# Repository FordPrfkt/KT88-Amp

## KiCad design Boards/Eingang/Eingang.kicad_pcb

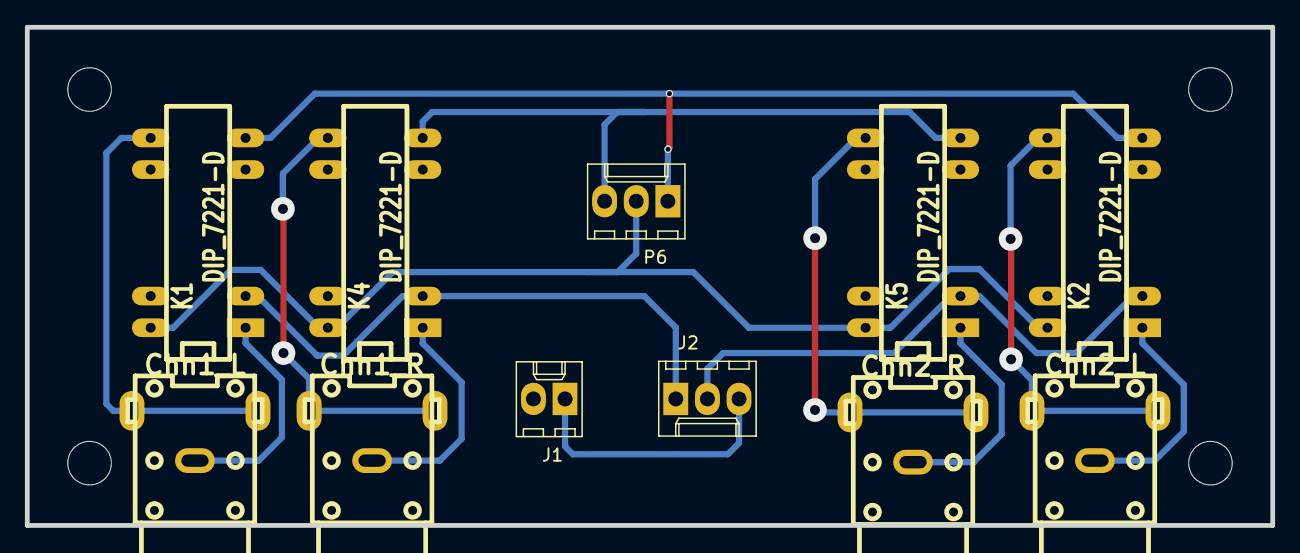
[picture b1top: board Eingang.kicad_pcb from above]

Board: 2 copper layers, 100.0 x 40.0 mm, 11 parts (0 on the bottom side), 15 nets.

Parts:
J1: 12V_Sup; Molex_KK-6410-02_02x2.54mm_Straight
J2: Chn_Switch; Molex_KK-6410-03_03x2.54mm_Straight
K1, K2, K4, K5: DIP_7221-D; REED
P6: LF_Out; Molex_KK-6410-03_03x2.54mm_Straight
P10: Chn1_L; rca_red
P11: Chn1_R; rca_white
P12: Chn2_L; rca_red
P13: Chn2_R; rca_white

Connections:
GND: J1.2, K1.6, K2.6, K4.6, K5.6
unnamed: J1.1, J2.3
unnamed: J2.1, K1.2, K4.2
unnamed: J2.2, K2.2, K5.2
unnamed: K1.1, P10.1
unnamed: K1.7, K2.7, P6.1
unnamed: K1.8, P10.2
unnamed: K1.14, K2.14, K4.14, K5.14, P6.2
unnamed: K2.1, P12.1
unnamed: K2.8, P12.2
unnamed: K4.1, P11.1
unnamed: K4.7, K5.7, P6.3
unnamed: K4.8, P11.2
unnamed: K5.1, P13.1
unnamed: K5.8, P13.2

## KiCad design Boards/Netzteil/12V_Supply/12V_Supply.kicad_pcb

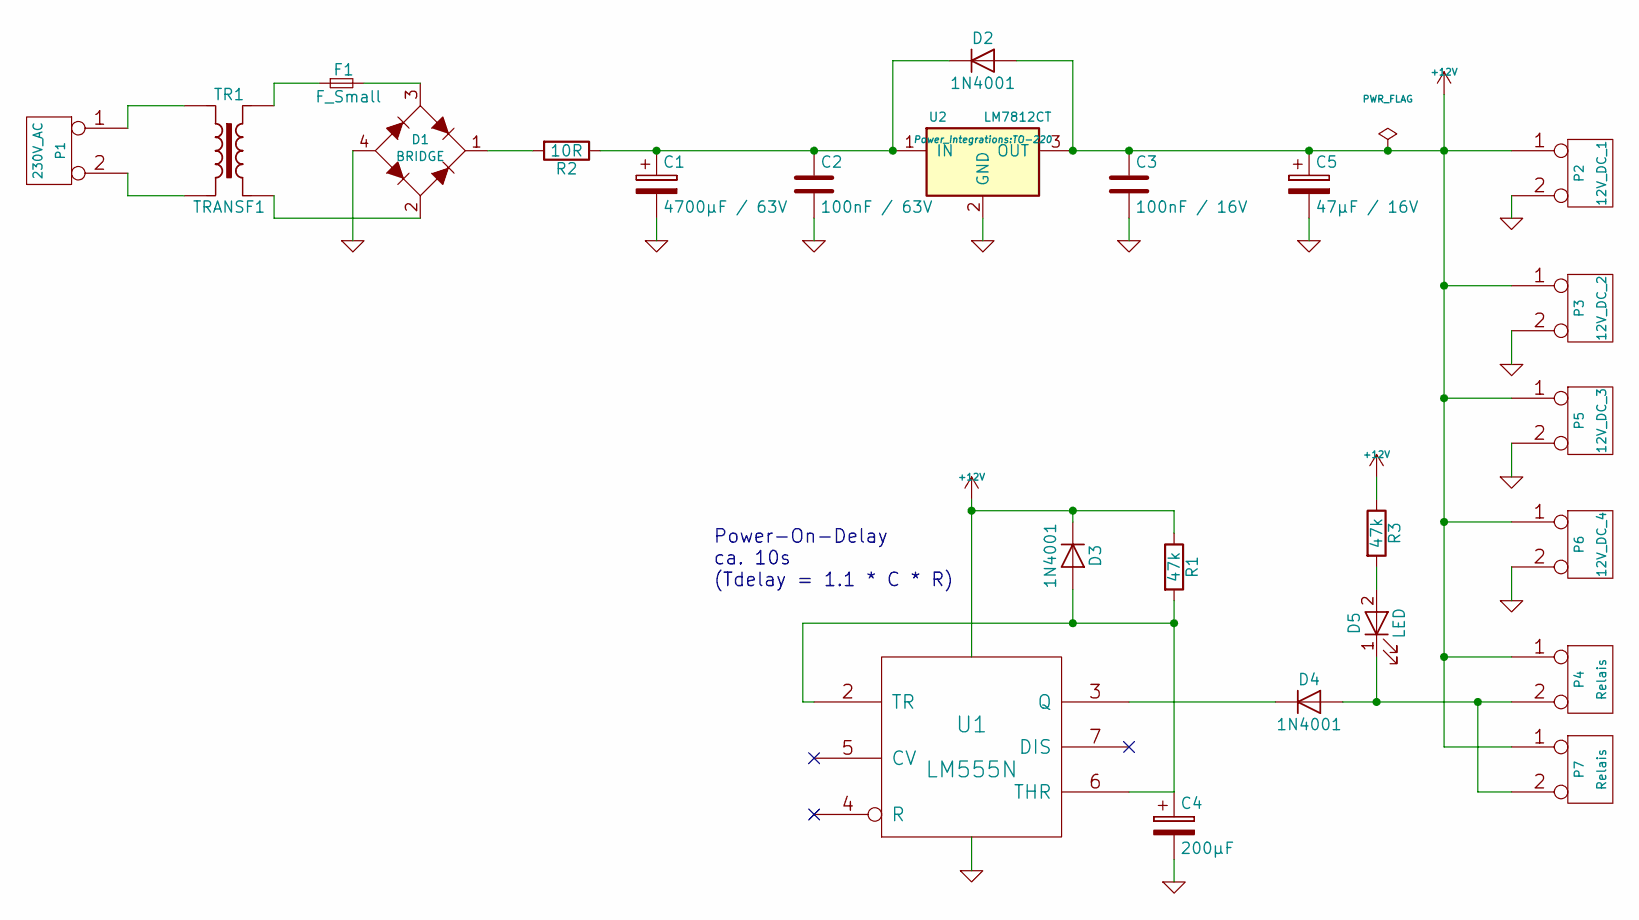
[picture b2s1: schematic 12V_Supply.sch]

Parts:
C1: 4700µF / 63V; CP_16x20mm
C2: 100nF / 63V; C_Disc_D3.0mm_W2.0mm_P2.50mm
C3: 100nF / 16V; C_Disc_D3.0mm_W2.0mm_P2.50mm
C4: 200µF; CP_4x5mm
C5: 47µF / 16V; CP_8x15mm
D1: BRIDGE; bridge_DFM
D2, D3, D4: 1N4001; diode_do41
D5: LED; LED_D3.0mm
F1: F_Small; fuse_holder_CQ-2
P1: 230V_AC; gmkds_3-2-7,62
P2: 12V_DC_1; MiniUniversalMate-N-LokSocket_2PinVertical
P3: 12V_DC_2; MiniUniversalMate-N-LokSocket_2PinVertical
P4, P7: Relais; kk156_26-60-4020
P5: 12V_DC_3; MiniUniversalMate-N-LokSocket_2PinVertical
P6: 12V_DC_4; MiniUniversalMate-N-LokSocket_2PinVertical
R1, R3: 47k; R_Axial_DIN0207_L6.3mm_D2.5mm_P10.16mm_Horizontal
R2: 10R; R_Axial_DIN0207_L6.3mm_D2.5mm_P10.16mm_Horizontal
TR1: TRANSF1; Transfo-simple
U1: LM555N; dil_8-300
U2: LM7812CT; TO-220

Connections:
+12V: C3.1, C5.1, D2.2 (A), D3.1 (K), P2.1, P3.1, P4.1, P5.1, P6.1, P7.1, R1.1, R3.1, U1.8 (VCC), U2.3 (OUT)
GND: C1.2, C2.2, C3.2, C4.2, C5.2, D1.4 (V-), P2.2, P3.2, P5.2, P6.2, U1.1 (GND), U2.2 (GND)
unnamed: C1.1, C2.1, D2.1 (K), R2.1, U2.1 (IN)
unnamed: C4.1, D3.2 (A), R1.2, U1.2 (TR), U1.6 (THR)
unnamed: D1.1 (V+), R2.2
unnamed: D1.2 (~1), TR1.3
unnamed: D1.3 (~2), F1.2
unnamed: D4.1 (K), U1.3 (Q)
unnamed: D4.2 (A), D5.1 (K), P4.2, P7.2
unnamed: D5.2 (A), R3.2
unnamed: F1.1, TR1.4
unnamed: P1.1, TR1.1
unnamed: P1.2, TR1.2

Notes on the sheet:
Power-On-Delay ca. 10s (Tdelay = 1.1 * C * R)

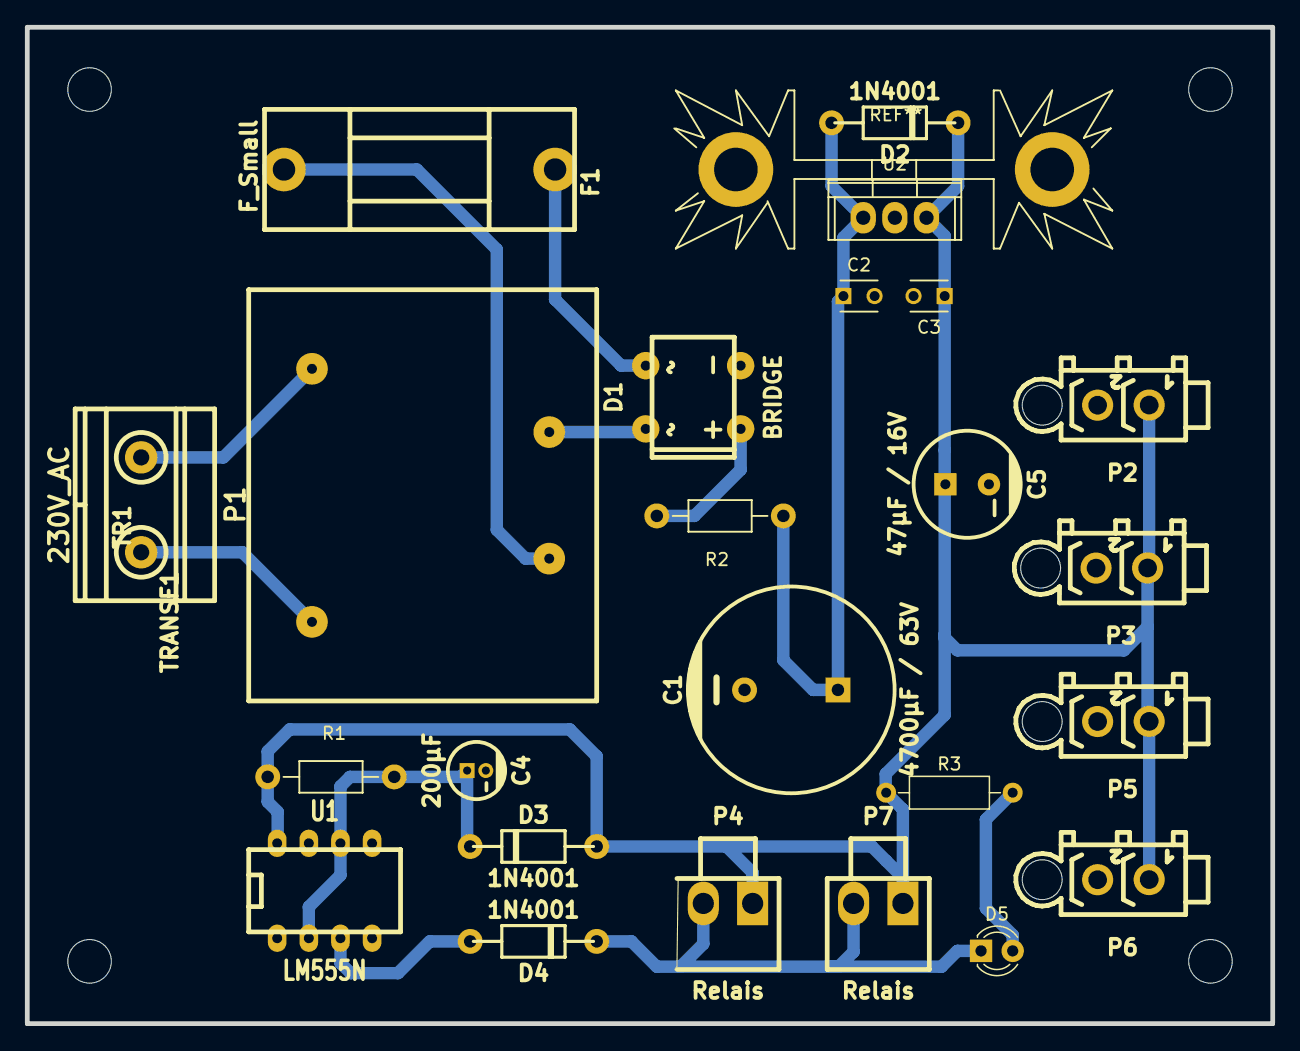
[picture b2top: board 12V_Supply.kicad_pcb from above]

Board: 2 copper layers, 100.0 x 80.0 mm, 24 parts (0 on the bottom side), 13 nets.

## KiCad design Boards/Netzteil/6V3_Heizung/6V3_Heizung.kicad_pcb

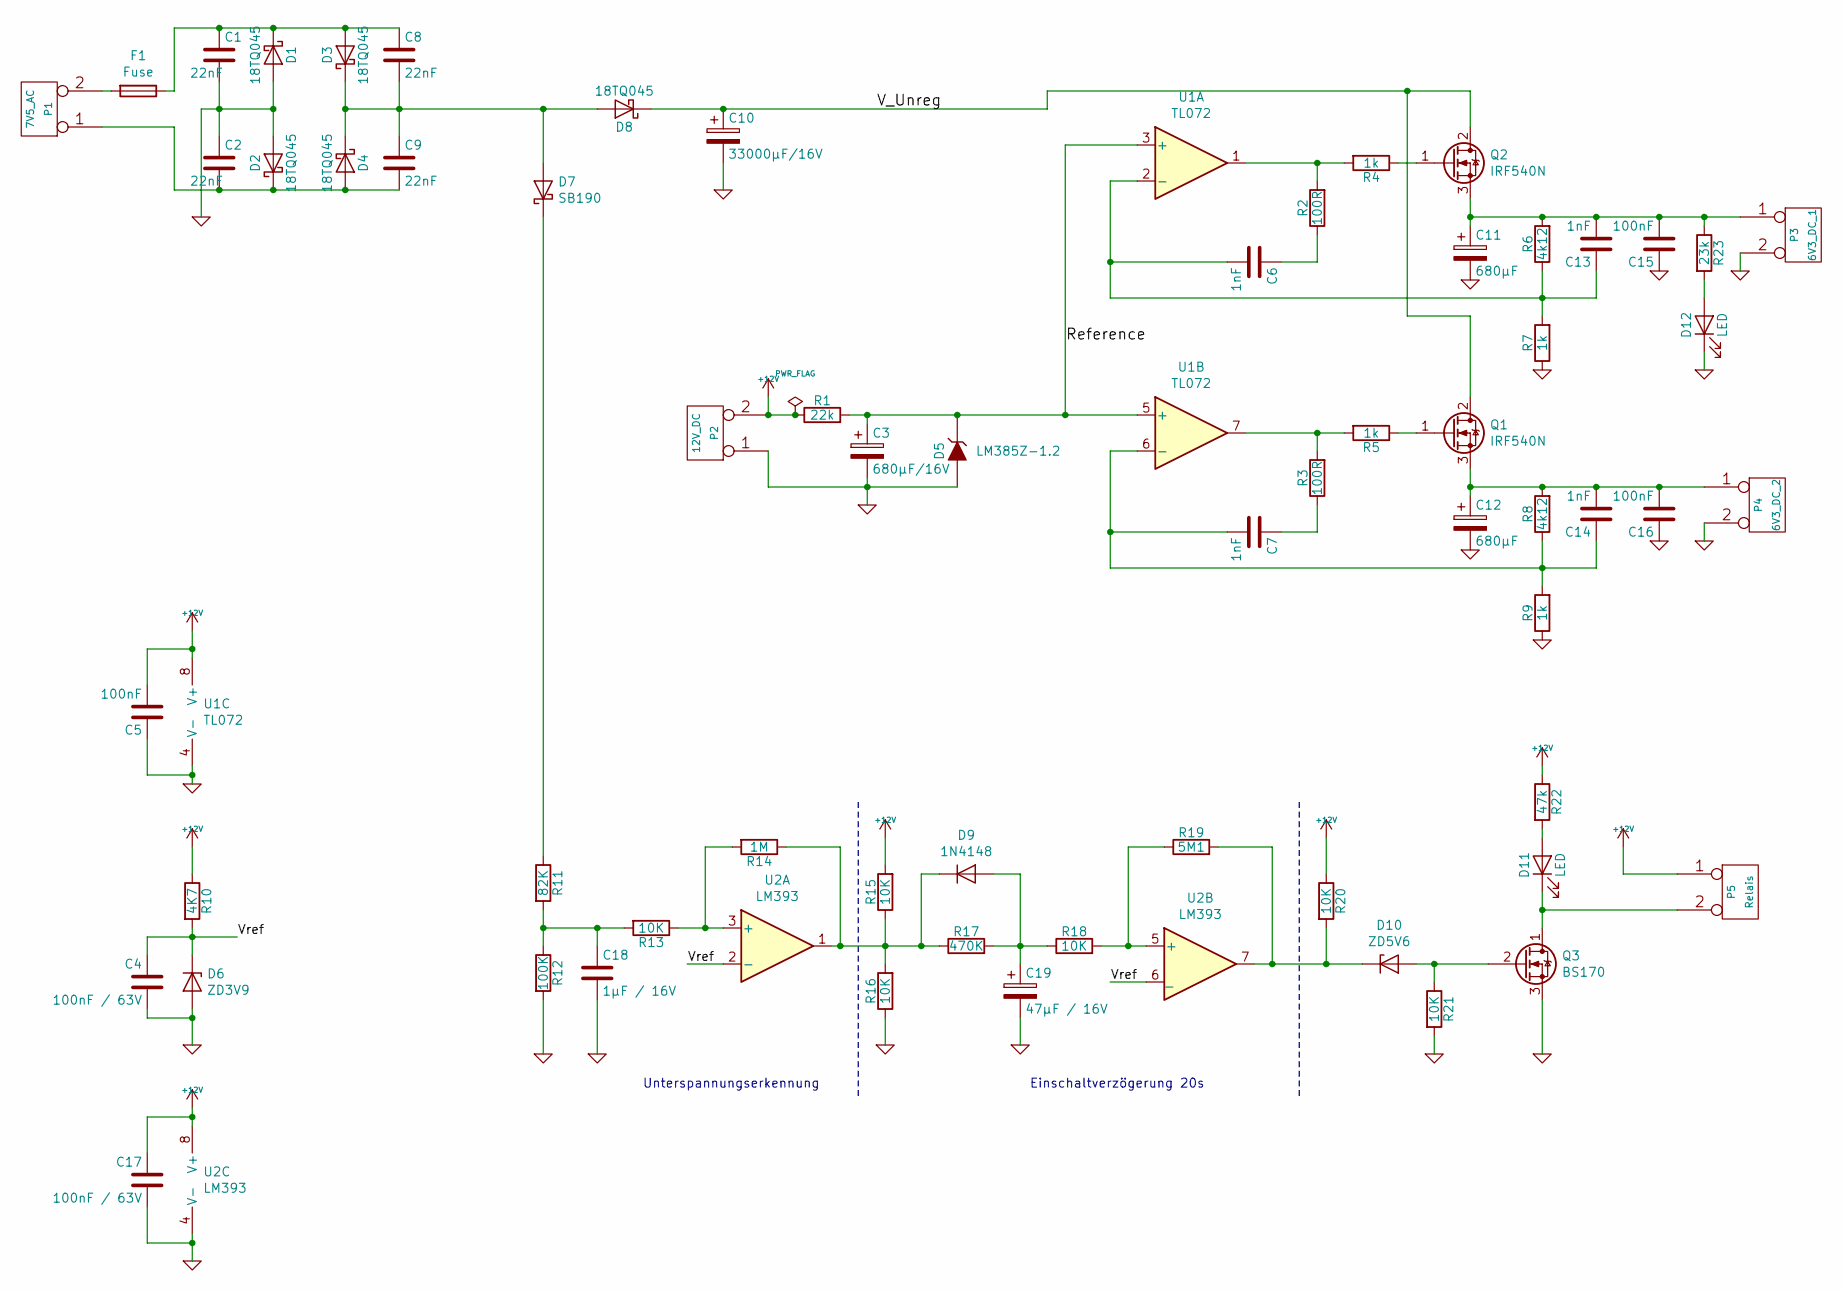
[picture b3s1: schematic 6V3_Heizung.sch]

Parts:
C1, C2, C8, C9: 22nF; C_Disc_D3.0mm_W2.0mm_P2.50mm
C3: 680µF/16V; CP_Radial_D10.0mm_P5.00mm
C4, C17: 100nF / 63V; C_Disc_D3.0mm_W2.0mm_P2.50mm
C5, C15, C16: 100nF; C_Disc_D3.0mm_W2.0mm_P2.50mm
C6, C7, C13, C14: 1nF; C_Disc_D3.0mm_W2.0mm_P2.50mm
C10: 33000µF/16V; CP_Radial_D18.0mm_P7.50mm
C11, C12: 680µF; CP_Radial_D10.0mm_P5.00mm
C18: 1µF / 16V; C_Disc_D3.0mm_W2.0mm_P2.50mm
C19: 47µF / 16V; CP_Radial_D8.0mm_P3.80mm
D1, D2, D3, D4, D8: 18TQ045; TO-220-2_Vertical
D5: LM385Z-1.2; TO-92-2
D6: ZD3V9; D_DO-35_SOD27_P10.16mm_Horizontal
D7: SB190; D_DO-41_SOD81_P10.16mm_Horizontal
D9: 1N4148; D_DO-35_SOD27_P10.16mm_Horizontal
D10: ZD5V6; D_DO-35_SOD27_P10.16mm_Horizontal
D11, D12: LED; LED_D3.0mm
F1: Fuse; fuse_holder_CQ-2
P1: 7V5_AC; TE_MATE-N-LOK_1-770866-x_1x02_P4.14mm_Vertical
P2: 12V_DC; Molex_KK-254_AE-6410-02A_1x02_P2.54mm_Vertical
P3: 6V3_DC_1; TE_MATE-N-LOK_1-770866-x_1x02_P4.14mm_Vertical
P4: 6V3_DC_2; TE_MATE-N-LOK_1-770866-x_1x02_P4.14mm_Vertical
P5: Relais; Molex_KK-254_AE-6410-02A_1x02_P2.54mm_Vertical
Q1, Q2: IRF540N; TO-220-3_Vertical
Q3: BS170; TO-92_Inline
R1: 22k; R_Axial_DIN0207_L6.3mm_D2.5mm_P10.16mm_Horizontal
R2, R3: 100R; R_Axial_DIN0207_L6.3mm_D2.5mm_P10.16mm_Horizontal
R4, R5, R7, R9: 1k; R_Axial_DIN0207_L6.3mm_D2.5mm_P10.16mm_Horizontal
R6, R8: 4k12; R_Axial_DIN0207_L6.3mm_D2.5mm_P10.16mm_Horizontal
R10: 4K7; R_Axial_DIN0207_L6.3mm_D2.5mm_P10.16mm_Horizontal
R11: 82K; R_Axial_DIN0207_L6.3mm_D2.5mm_P10.16mm_Horizontal
R12: 100K; R_Axial_DIN0207_L6.3mm_D2.5mm_P10.16mm_Horizontal
R13, R15, R16, R18, R20, R21: 10K; R_Axial_DIN0207_L6.3mm_D2.5mm_P10.16mm_Horizontal
R14: 1M; R_Axial_DIN0207_L6.3mm_D2.5mm_P10.16mm_Horizontal
R17: 470K; R_Axial_DIN0207_L6.3mm_D2.5mm_P10.16mm_Horizontal
R19: 5M1; R_Axial_DIN0207_L6.3mm_D2.5mm_P10.16mm_Horizontal
R22: 47k; R_Axial_DIN0207_L6.3mm_D2.5mm_P10.16mm_Horizontal
R23: 23k; R_Axial_DIN0207_L6.3mm_D2.5mm_P10.16mm_Horizontal
U1: TL072; DIP-8_W7.62mm
U2: LM393; DIP-8_W7.62mm

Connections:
+12V: C5.2, C17.1, P2.2, P5.1, R1.1, R10.1, R15.2, R20.1, R22.1, U1.8 (V+), U2.8 (V+)
/Reference: C3.1, D5.1 (K), R1.2, U1.3 (+), U1.5 (+)
/V_Unreg: C10.1, D8.1 (K), Q1.2 (D), Q2.2 (D)
/Vref: C4.1, D6.1 (K), R10.2, U2.2 (-), U2.6 (_)
GND: C1.2, C2.1, C3.2, C4.2, C5.1, C10.2, C11.2, C12.2, C15.1, C16.1, C17.2, C18.2, C19.2, D1.2 (A), D2.2 (A), D5.2 (A), D6.2 (A), D12.1 (K), P2.1, P3.2, P4.2, Q3.3 (S), R7.1, R9.1, R12.2, R16.1, R21.2, U1.4 (V-), U2.4 (V-)
unnamed: C1.1, C8.1, D1.1 (K), D3.2 (A), F1.1
unnamed: C2.2, C9.2, D2.1 (K), D4.2 (A), P1.1
unnamed: C6.1, R2.1
unnamed: C7.1, R3.1
unnamed: C8.2, C9.1, D3.1 (K), D4.1 (K), D7.2 (A), D8.2 (A)
unnamed: C11.1, C13.2, C15.2, P3.1, Q2.3 (S), R6.2, R23.1
unnamed: C12.1, C14.2, C16.2, P4.1, Q1.3 (S), R8.2
unnamed: C6.2, C13.1, R6.1, R7.2, U1.2 (-)
unnamed: C7.2, C14.1, R8.1, R9.2, U1.6 (-)
unnamed: C18.1, R11.2, R12.1, R13.2
unnamed: C19.1, D9.2 (A), R17.2, R18.1
unnamed: D7.1 (K), R11.1
unnamed: D9.1 (K), R14.1, R15.1, R16.2, R17.1, U2.1
unnamed: D10.1 (K), R19.2, R20.2, U2.7
unnamed: D10.2 (A), Q3.2 (G), R21.1
unnamed: D11.1 (K), P5.2, Q3.1 (D)
unnamed: D11.2 (A), R22.2
unnamed: D12.2 (A), R23.2
unnamed: F1.2, P1.2
unnamed: Q1.1 (G), R5.1
unnamed: Q2.1 (G), R4.1
unnamed: R2.2, R4.2, U1.1
unnamed: R3.2, R5.2, U1.7
unnamed: R13.1, R14.2, U2.3 (+)
unnamed: R18.2, R19.1, U2.5 (+)

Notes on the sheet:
Unterspannungserkennung
Einschaltverzögerung 20s

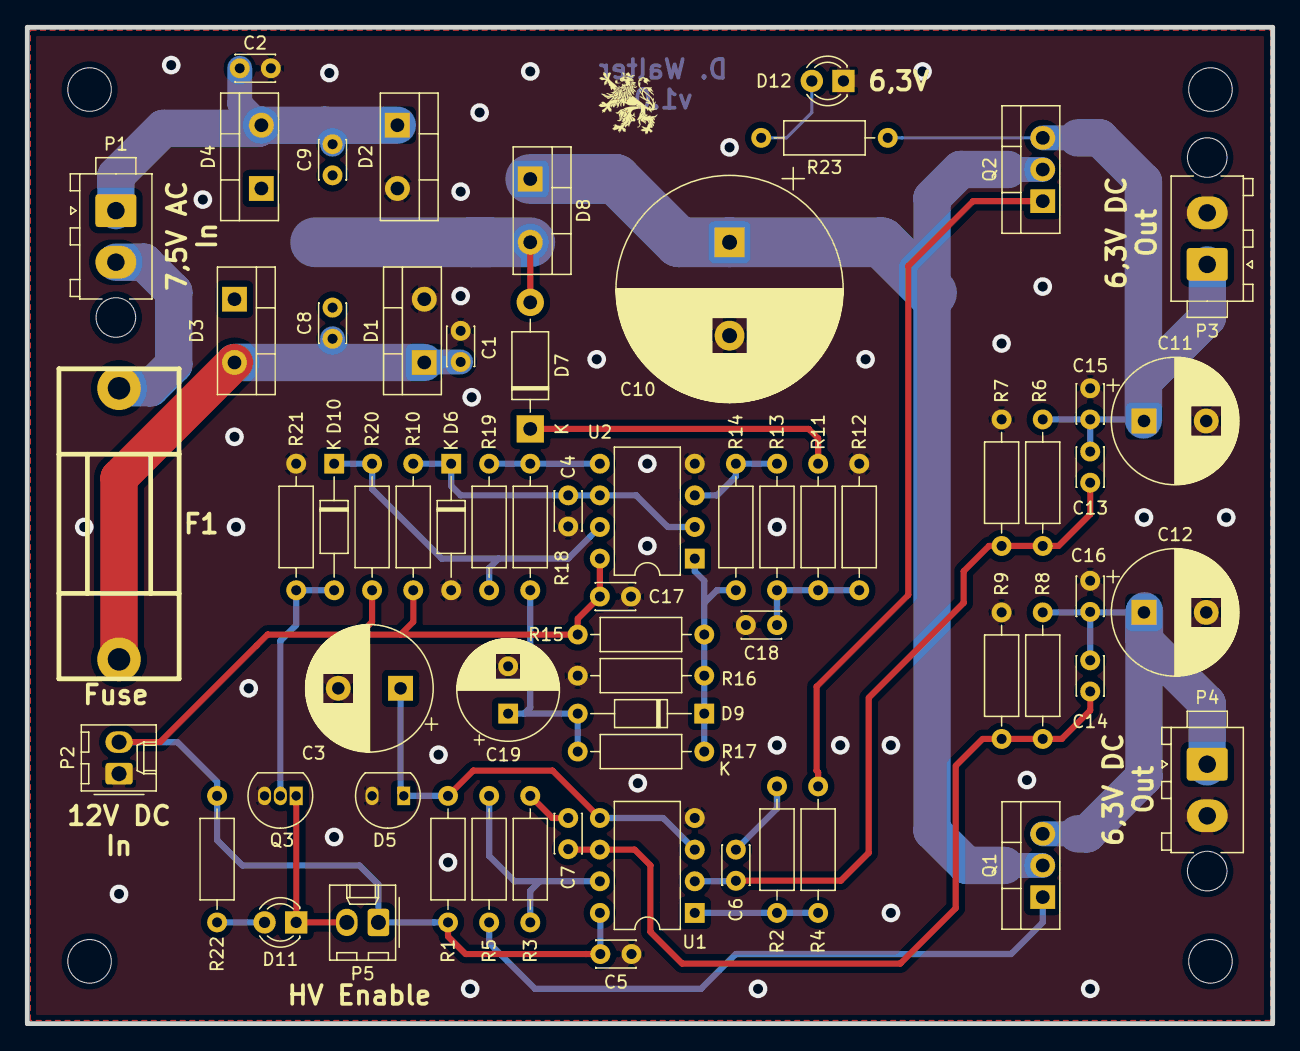
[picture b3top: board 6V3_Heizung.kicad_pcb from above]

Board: 2 copper layers, 100.0 x 80.0 mm, 65 parts (0 on the bottom side), 30 nets.

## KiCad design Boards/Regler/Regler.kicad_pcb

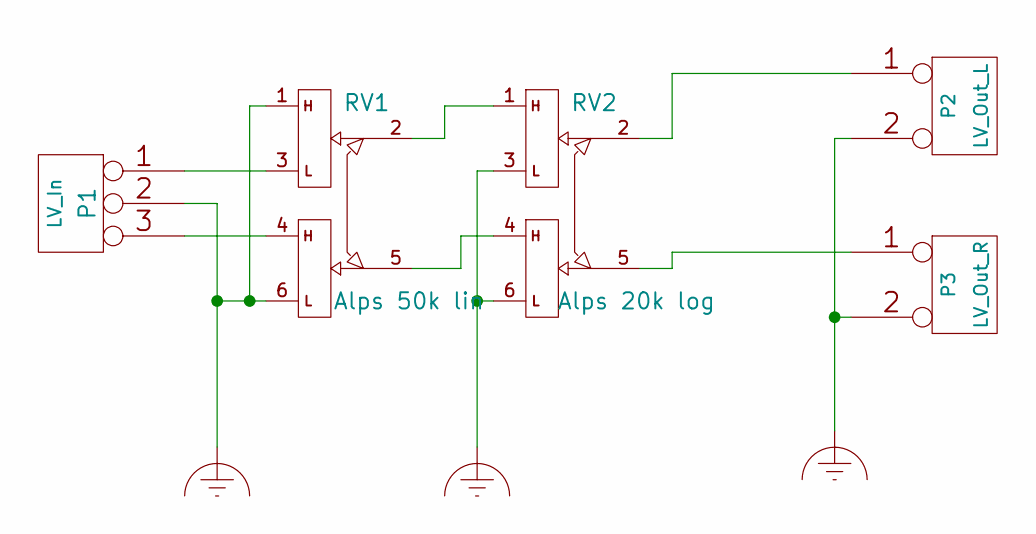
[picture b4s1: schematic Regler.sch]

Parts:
P1: LV_In; Molex_KK-6410-03_03x2.54mm_Straight
P2: LV_Out_L; Molex_KK-6410-02_02x2.54mm_Straight
P3: LV_Out_R; Molex_KK-6410-02_02x2.54mm_Straight
RV1: Alps 50k lin; Potentiometer_Alps-RK271-double
RV2: Alps 20k log; Potentiometer_Alps-RK271-double

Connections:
Earth_Clean: P1.2, P2.2, P3.2, RV1.1, RV1.6, RV2.3, RV2.6
unnamed: P1.1, RV1.3
unnamed: P1.3, RV1.4
unnamed: P2.1, RV2.2
unnamed: P3.1, RV2.5
unnamed: RV1.2, RV2.1
unnamed: RV1.5, RV2.4

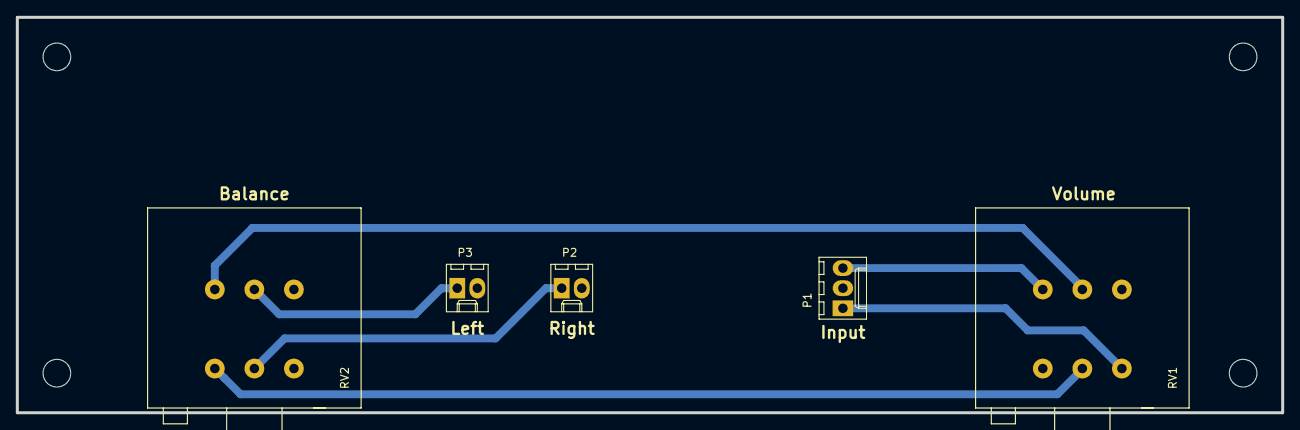
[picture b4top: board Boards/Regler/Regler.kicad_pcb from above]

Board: 2 copper layers, 160.0 x 50.0 mm, 5 parts (0 on the bottom side), 7 nets.

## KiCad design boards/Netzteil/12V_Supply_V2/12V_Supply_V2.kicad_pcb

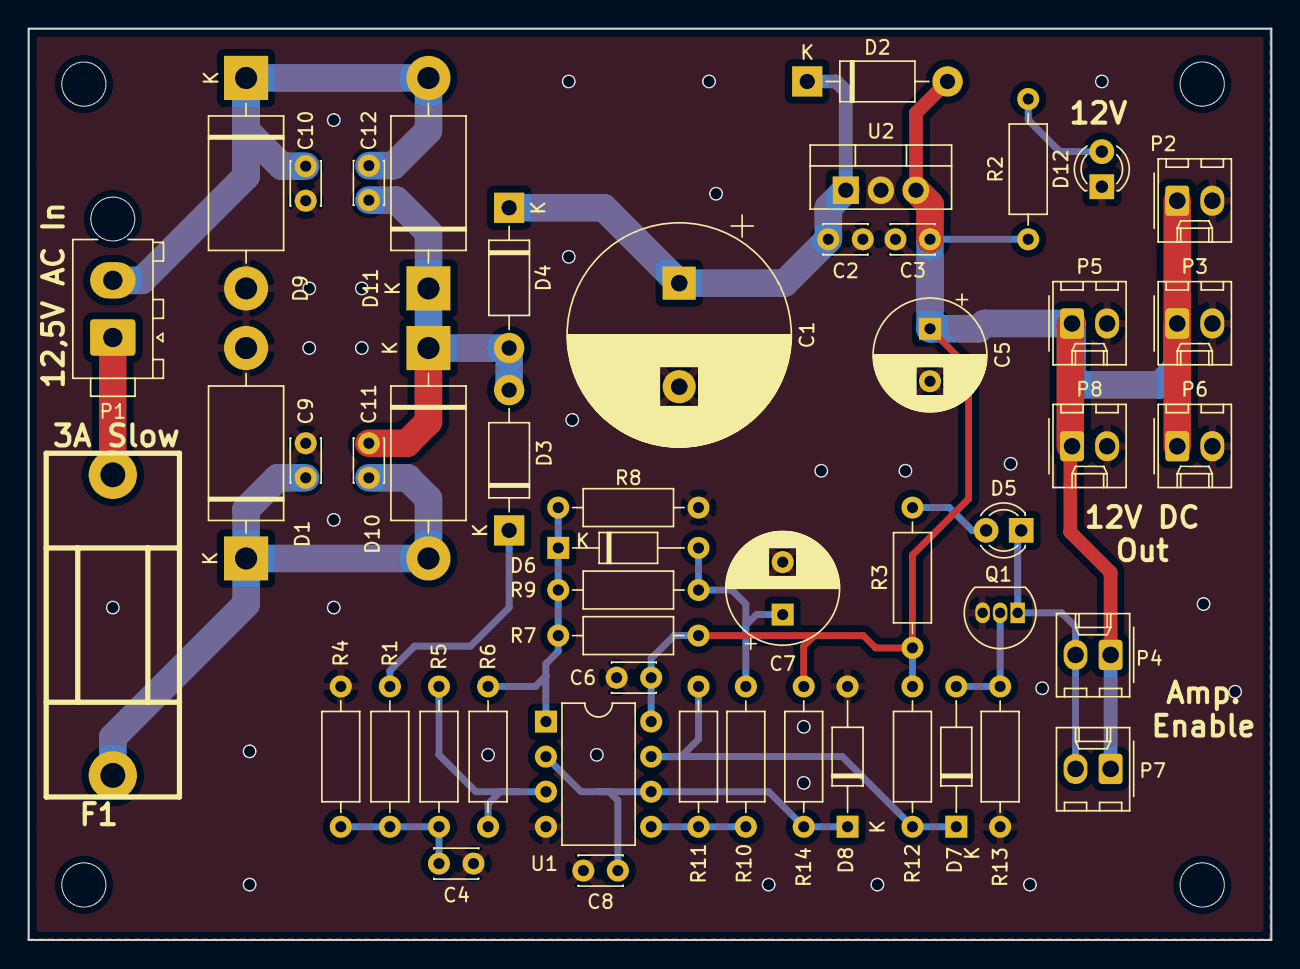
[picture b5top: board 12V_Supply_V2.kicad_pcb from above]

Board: 2 copper layers, 90.0 x 66.0 mm, 50 parts (0 on the bottom side), 19 nets.

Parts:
C1: 4700µF / 63V; CP_Radial_D16.0mm_P7.50mm
C2, C6, C8: 100nF / 63V; C_Disc_D3.0mm_W2.0mm_P2.50mm
C3: 100nF / 16V; C_Disc_D3.0mm_W2.0mm_P2.50mm
C4: 1µF / 16V; C_Disc_D3.0mm_W2.0mm_P2.50mm
C5, C7: 47µF / 16V; CP_Radial_D8.0mm_P3.80mm
C9, C10, C11, C12: 22nF; C_Disc_D3.0mm_W2.0mm_P2.50mm
D1, D9, D10, D11: SB350; D_DO-201AD_P15.24mm_Horizontal
D2: 1N4001; D_DO-41_SOD81_P10.16mm_Horizontal
D3: SB190; D_DO-41_SOD81_P10.16mm_Horizontal
D4: SB350; D_DO-41_SOD81_P10.16mm_Horizontal
D5, D12: LED; LED_D3.0mm
D6: 1N4148; D_DO-35_SOD27_P10.16mm_Horizontal
D7: ZD5V6; D_DO-35_SOD27_P10.16mm_Horizontal
D8: ZD3V9; D_DO-35_SOD27_P10.16mm_Horizontal
F1: 3A Slow; fuse_holder_CQ-2
P1: 12V_AC; TE_MATE-N-LOK_1-770866-x_1x02_P4.14mm_Vertical
P2: 12V_DC_1; Molex_KK-254_AE-6410-02A_1x02_P2.54mm_Vertical
P3: 12V_DC_2; Molex_KK-254_AE-6410-02A_1x02_P2.54mm_Vertical
P4, P7: Relais; Molex_KK-254_AE-6410-02A_1x02_P2.54mm_Vertical
P5: 12V_DC_3; Molex_KK-254_AE-6410-02A_1x02_P2.54mm_Vertical
P6, P8: 12V_DC_4; Molex_KK-254_AE-6410-02A_1x02_P2.54mm_Vertical
Q1: BS170; TO-92_Inline
R1: 82K; R_Axial_DIN0207_L6.3mm_D2.5mm_P10.16mm_Horizontal
R2, R3: 47k; R_Axial_DIN0207_L6.3mm_D2.5mm_P10.16mm_Horizontal
R4: 100K; R_Axial_DIN0207_L6.3mm_D2.5mm_P10.16mm_Horizontal
R5, R7, R8, R10, R12, R13: 10K; R_Axial_DIN0207_L6.3mm_D2.5mm_P10.16mm_Horizontal
R6: 1M; R_Axial_DIN0207_L6.3mm_D2.5mm_P10.16mm_Horizontal
R9: 470K; R_Axial_DIN0207_L6.3mm_D2.5mm_P10.16mm_Horizontal
R11: 5M1; R_Axial_DIN0207_L6.3mm_D2.5mm_P10.16mm_Horizontal
R14: 4K7; R_Axial_DIN0207_L6.3mm_D2.5mm_P10.16mm_Horizontal
U1: LM393; DIP-8_W7.62mm
U2: LM7812CT; TO-220-3_Vertical

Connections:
+12V: C3.1, C5.1, C6.1, D2.2, P2.1, P3.1, P4.1, P5.1, P6.1, P7.1, P8.1, R2.1, R3.1, R7.2, R12.1, R14.1, U1.8, U2.3
/Vref: C8.1, D8.1, R14.2, U1.2, U1.6
GND: C1.2, C2.2, C3.2, C4.2, C5.2, C6.2, C7.2, C8.2, C9.2, C10.1, D1.2, D8.2, D9.2, D12.1, P2.2, P3.2, P5.2, P6.2, P8.2, Q1.3, R4.2, R8.1, R13.2, U1.4, U2.2
unnamed: C1.1, C2.1, D2.1, D4.1, U2.1
unnamed: C4.1, R1.2, R4.1, R5.2
unnamed: C7.1, D6.2, R9.2, R10.1
unnamed: C10.2, C12.2, D9.1, D11.2, P1.2
unnamed: C9.1, C11.1, D1.1, D10.2, F1.2
unnamed: C11.2, C12.1, D3.2, D4.2, D10.1, D11.1
unnamed: D3.1, R1.1
unnamed: D5.1, P4.2, P7.2, Q1.1
unnamed: D5.2, R3.2
unnamed: D6.1, R6.1, R7.1, R8.2, R9.1, U1.1
unnamed: D7.1, R11.2, R12.2, U1.7
unnamed: D7.2, Q1.2, R13.1
unnamed: D12.2, R2.2
unnamed: F1.1, P1.1
unnamed: R5.1, R6.2, U1.3
unnamed: R10.2, R11.1, U1.5

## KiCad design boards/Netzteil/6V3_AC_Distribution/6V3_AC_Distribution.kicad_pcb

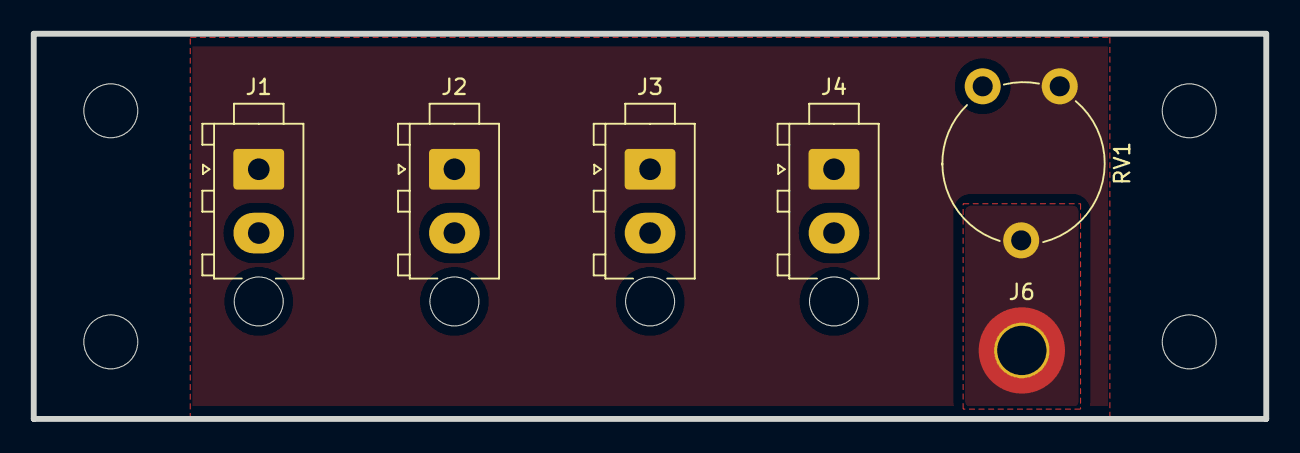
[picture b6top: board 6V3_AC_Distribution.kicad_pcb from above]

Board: 2 copper layers, 80.0 x 25.0 mm, 6 parts (0 on the bottom side), 3 nets, no tracks yet.

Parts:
J1, J2, J3, J4: Conn_01x02; TE_MATE-N-LOK_1-770866-x_1x02_P4.14mm_Vertical
J6: Screw_Terminal_01x01; MountingHole_3.2mm_M3_DIN965_Pad_TopOnly
RV1: R_POT; Potentiometer_Piher_PT-10-V10_Vertical

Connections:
GND: J6.1, RV1.2
unnamed: J1.1, J2.1, J3.1, J4.1, RV1.3
unnamed: J1.2, J2.2, J3.2, J4.2, RV1.1

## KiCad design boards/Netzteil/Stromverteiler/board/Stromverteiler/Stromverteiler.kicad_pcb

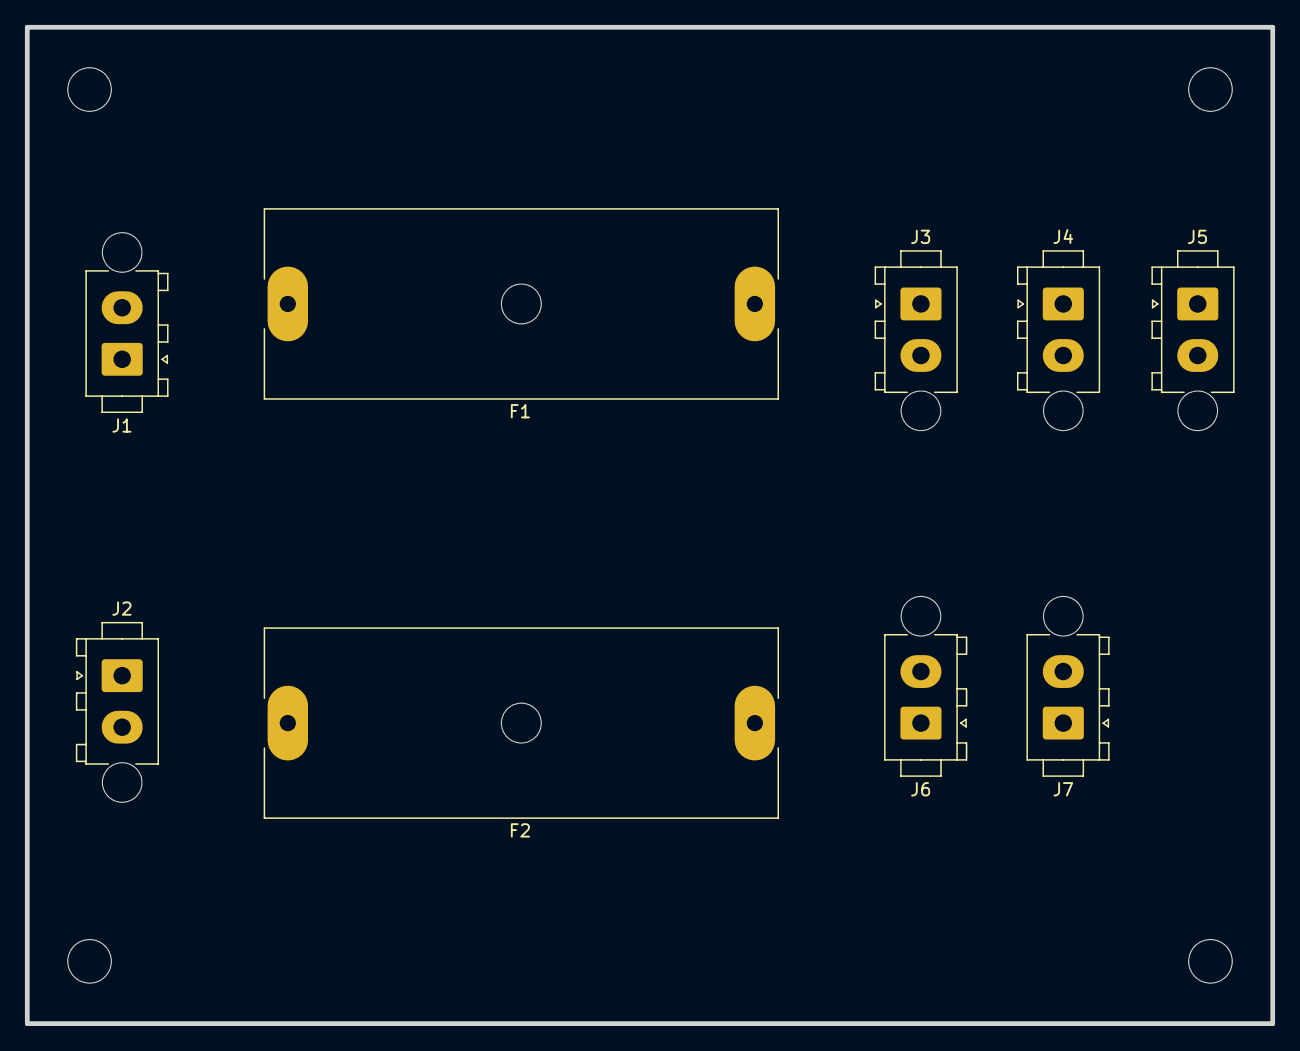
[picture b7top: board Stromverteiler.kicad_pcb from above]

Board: 2 copper layers, 100.0 x 80.0 mm, 9 parts (0 on the bottom side), 6 nets, no tracks yet.

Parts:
F1, F2: Fuse; Fuseholder_Cylinder-6.3x32mm_Schurter_0031-8002_Horizontal_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
J1: 6V3AC_In; TE_MATE-N-LOK_1-770866-x_1x02_P4.14mm_Vertical
J2: 450VAC_In; TE_MATE-N-LOK_1-770866-x_1x02_P4.14mm_Vertical
J3: 6V3AC_Out1; TE_MATE-N-LOK_1-770866-x_1x02_P4.14mm_Vertical
J4: 6V3AC_Out2; TE_MATE-N-LOK_1-770866-x_1x02_P4.14mm_Vertical
J5: 6V3AC_Out3; TE_MATE-N-LOK_1-770866-x_1x02_P4.14mm_Vertical
J6: 450VAC_Out1; TE_MATE-N-LOK_1-770866-x_1x02_P4.14mm_Vertical
J7: 450VAC_Out2; TE_MATE-N-LOK_1-770866-x_1x02_P4.14mm_Vertical

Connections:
unnamed: F1.1, J3.1, J4.1, J5.1
unnamed: F1.2, J1.2
unnamed: F2.1, J6.1, J7.1
unnamed: F2.2, J2.2
unnamed: J1.1, J3.2, J4.2, J5.2
unnamed: J2.1, J6.2, J7.2

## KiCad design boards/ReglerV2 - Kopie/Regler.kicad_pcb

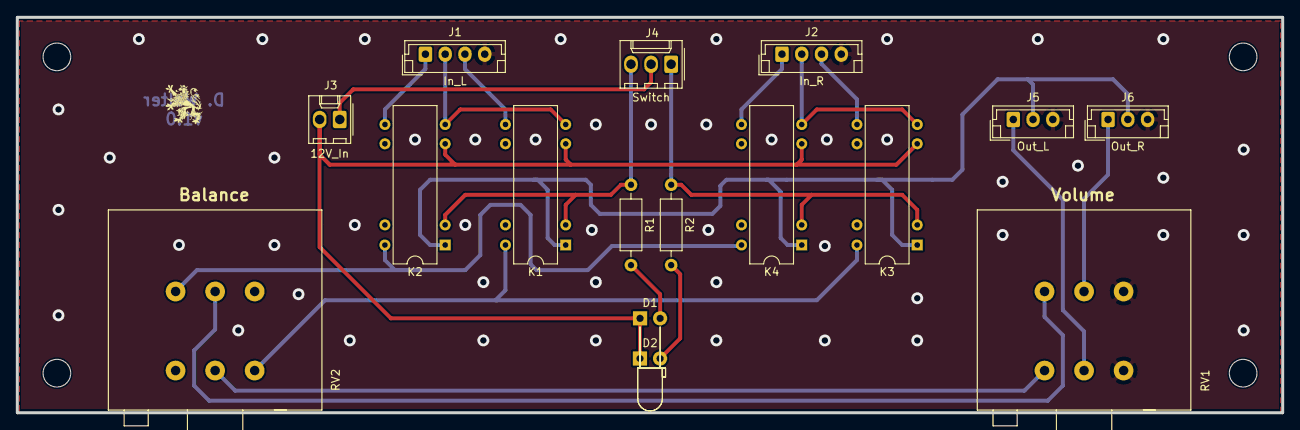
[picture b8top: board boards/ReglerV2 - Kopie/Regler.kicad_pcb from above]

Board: 2 copper layers, 160.0 x 50.0 mm, 16 parts (0 on the bottom side), 20 nets.

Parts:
D1: LED_1 Gn; LED_D3.0mm_Horizontal_O6.35mm_Z6.0mm
D2: LED_2 Gn; LED_D3.0mm_Horizontal_O1.27mm_Z6.0mm
J1: In_L; JST_EH_B4B-EH-A_1x04_P2.50mm_Vertical
J2: In_R; JST_EH_B4B-EH-A_1x04_P2.50mm_Vertical
J3: 12V_In; Molex_KK-254_AE-6410-02A_1x02_P2.54mm_Vertical
J4: Switch; Molex_KK-254_AE-6410-03A_1x03_P2.54mm_Vertical
J5: Out_L; JST_EH_B3B-EH-A_1x03_P2.50mm_Vertical
J6: Out_R; JST_EH_B3B-EH-A_1x03_P2.50mm_Vertical
K1, K2, K3, K4: DIPxx-2Axx-21x; Relay_StandexMeder_DIP_LowProfile
R1, R2: 560R; R_Axial_DIN0207_L6.3mm_D2.5mm_P10.16mm_Horizontal
RV1: Alps 20k log; Potentiometer_Alps-RK271-double
RV2: Alps 50k lin; Potentiometer_Alps-RK271-double

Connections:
+12V: J3.1, J4.2
/CH_1: J4.3, K1.2, K2.2, R1.1
/CH_2: J4.1, K3.2, K4.2, R2.1
/GND_1: J1.2, K1.7, K2.7
/GND_2: J2.2, K3.7, K4.7
/L_1: J1.3, K1.8
/L_2: J2.3, K3.8
/L_Out: J5.1, RV1.2
/L_Sw: K1.14, K3.14, RV2.3
/R_1: J1.1, K2.8
/R_2: J2.1, K4.8
/R_Out: J6.1, RV1.5
/R_Sw: K2.14, K4.14, RV2.4
Earth_Clean: J1.4, J2.4, J5.3, J6.3, RV1.3, RV1.6
GND: D1.1, D2.1, J3.2, K1.6, K2.6, K3.6, K4.6
GNDS: J5.2, J6.2, K1.1, K2.1, K3.1, K4.1
unnamed: D1.2, R1.2
unnamed: D2.2, R2.2
unnamed: RV1.1, RV2.2
unnamed: RV1.4, RV2.5
